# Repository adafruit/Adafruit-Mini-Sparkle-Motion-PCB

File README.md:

## Adafruit Mini Sparkle Motion - WLED-friendly ESP32 NeoPixel LED Driver PCB

<a href="http://www.adafruit.com/products/6160"><br/>
Click here to purchase one from the Adafruit shop</a>

PCB files for the Adafruit Mini Sparkle Motion - WLED-friendly ESP32 NeoPixel LED Driver. 

Format is EagleCAD schematic and board layout
* https://www.adafruit.com/product/6160

### Description

The Adafruit Sparkle Motion Mini is part of our series of "Sparkle Motion" boards, that are our attempt to make the best small WLED-friendly smart LED driving board in the whole world. Our resident mermaid, firepixie makes a lot of projects with WLED and she loves it! So how can we make something that will be powerful enough to drive advanced LED projects that need a compact design?

The Mini version of the Sparkle Motion is a simpler version of our full-featured Sparkle Motion, we give up the high voltage support and built in IR receiver, in order to make it under 1 square inch in size! By using a 4-layer board and double-sided assembly we've put together this feature set:

* Power via USB Type C for up to 5V 4A input - you can use off-the-shelf USB battery packs for portable operation.
* 4 Amp resetting fuse to protect from over-current drive
* ESP32 mini module with built in antenna port - the classic ESP32 has the best WLED support even if we'd prefer the 'S2 or 'S3. Comes with 4 MB of flash, dual core 240MHz Tensilica, WiFi, Bluetooth LE and Bluetooth Classic support.
* USB-serial converter with auto-reset
* Two output signals plus 5V power and ground - both signal output are level shifted to 5V. These are on 0.1" spaced breakout pads. To keep the design slim we don't include terminal blocks pre-soldered, but we do stock the matching blocks if you want them
* Extra 2x3 0.1" breakout pads with 4 more GPIO plus 3V power and ground.
* Built-in I2S microphone
* Stemma QT I2C port to connect external sensors/OLED/etc
* User button on GPIO 0 plus Reset button
* Red built-in LED on pin 12
* Small built-in NeoPixel on pin 18 
* Separate analog/digital input JST port for analog input, potentiometer, microphone or external IR receiver on pin 13
* Compact enough you can use it for wearable projects - 1.2"x0.8" / 30mm x 20mm size with mounting holes

While we recommend it for use with WLED, it will also work just fine as a compact ESP32 board for use with Arduino, ESP-IDF, MicroPython, CircuitPython or any other ESP32 supported codebase. 

Note that unlike the classic Sparkle Motion board, we don't include terminal blocks pre-soldered to keep the board very slim. We do stock the matching blocks if you want them, a small amount of soldering is required to attach them. Also, unlike the bigger version, we dropped the on-board IR receiver - however its easy to add one by plugging in a JST SH 3-pin socket cable and slotting in an IR receiver module.

### License

Adafruit invests time and resources providing this open source design, please support Adafruit and open-source hardware by purchasing products from [Adafruit](https://www.adafruit.com)!

Designed by Limor Fried/Ladyada for Adafruit Industries.

Creative Commons Attribution/Share-Alike, all text above must be included in any redistribution. 
See license.txt for additional details.

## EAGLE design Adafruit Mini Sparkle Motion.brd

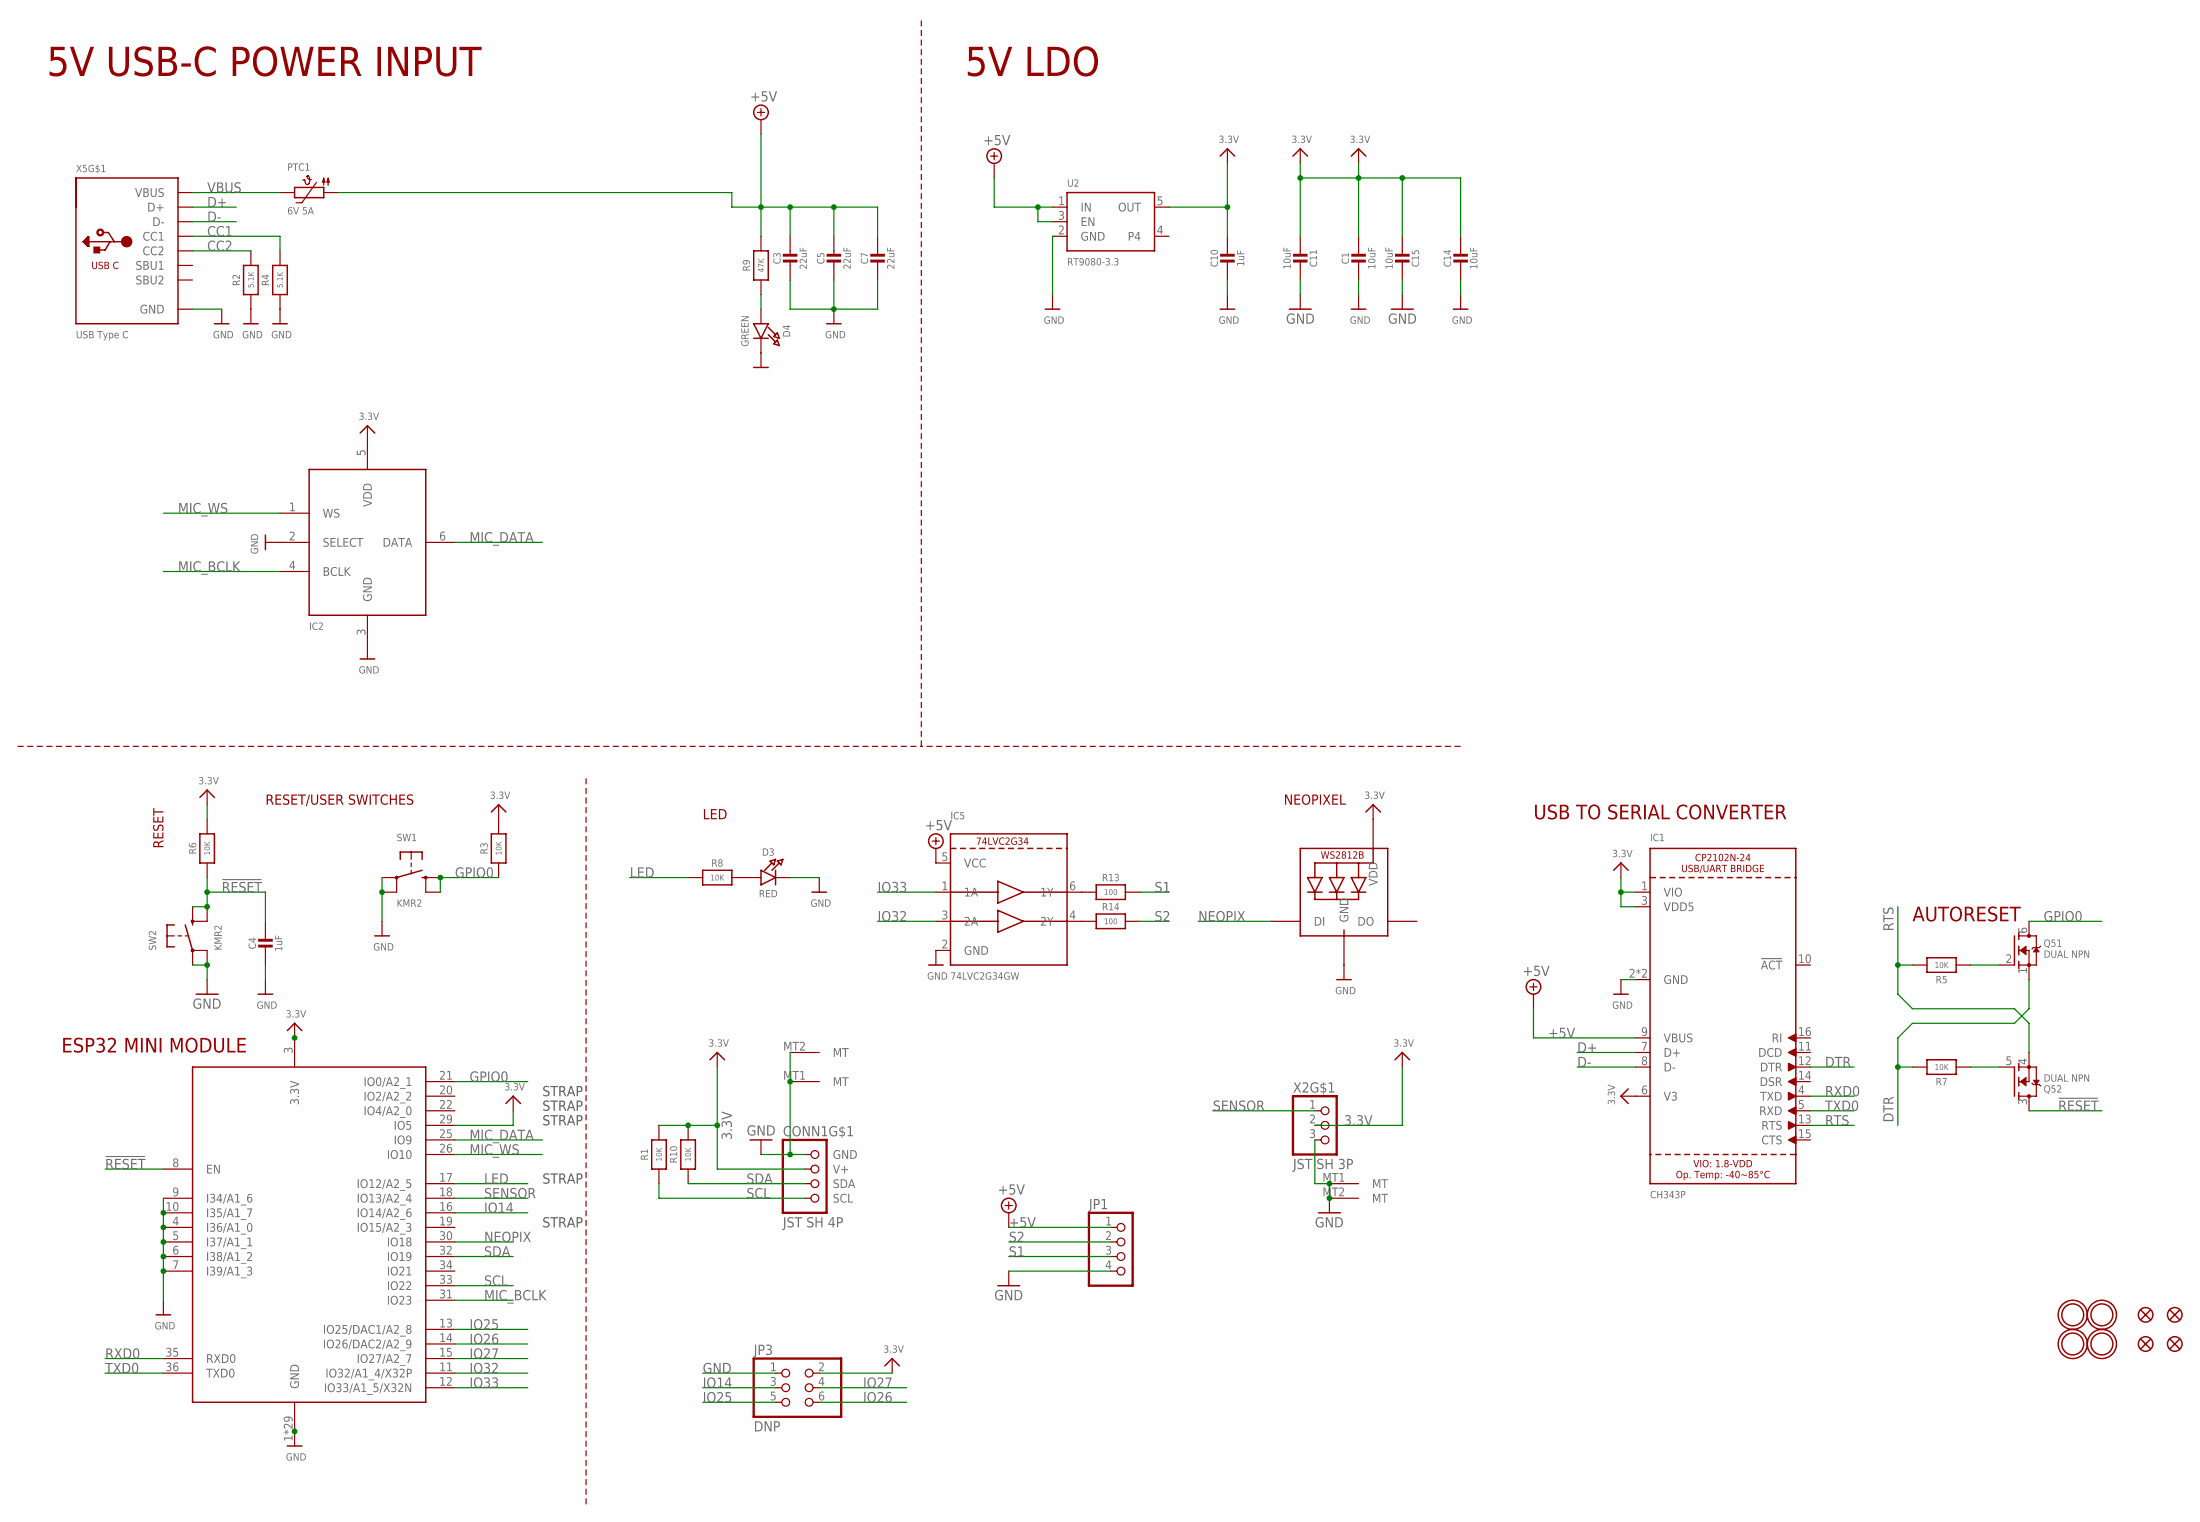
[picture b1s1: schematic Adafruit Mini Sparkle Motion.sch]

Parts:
C1, C11, C14, C15: 10uF; 0805-NO
C3, C5, C7: 22uF; 0805-NO
C4, C10: 1uF; _0402NO
CONN1: JST SH 4P; JST_SH4
D3: RED; CHIPLED_0603_NOOUTLINE
D4: GREEN; CHIPLED_0603_NOOUTLINE
IC1: CH343P; QFN16_3MM
IC2: ICS-43434; SPH0645LM4H
IC5: 74LVC2G34GW; SC70-6L
JP1: HEADER-1X4; 1X04_OVAL
JP3: DNP; 2X03_ROUND_70MIL
LED1: WS2812B_SK6805_1515; SK6805_1515
PTC1: 6V 5A; PTC1210
Q5: DUAL NPN; SOT363; JLC_ROTATION 90
R1, R3, R5, R6, R7, R8, R10: 10K; _0402NO
R2, R4: 5.1K; _0402NO
R9: 47K; _0402NO
R13, R14: 100; _0402NO
SW1, SW2: KMR2; BTN_RKB2_4.6X2.8
U2: RT9080-3.3; SOT23-5; JLC_ROTATION 0
U$14, U$20, U$28, U$31: MOUNTINGHOLE2.5; MOUNTINGHOLE_2.5_PLATED
U$23, U$25, U$34, U$35: FIDUCIAL_0.5MM
X2: JST SH 3P; JST_SH3
X4: ESP32-MINI-1
X5: USB Type C; USB_C_CUSB31-CFM2AX-01-X

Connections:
3.3V: C1.1, C10.1, C11.1, C14.1, C15.1, CONN1.2 (V+), IC1.1 (VIO), IC1.3 (VDD5), IC1.6 (V3), IC2.5 (VDD), JP3.2, LED1.2 (VDD), R1.2, R3.2, R6.2, R10.2, U2.5 (OUT), X2.2, X4.3 (3.3V), X4.29 (IO5)
!RESET: C4.1, Q5.3 (D), R6.1, SW2.B (S), SW2.B' (S1), X4.8 (EN)
+5V: C3.1, C5.1, C7.1, IC1.9 (VBUS), IC5.5 (VCC), JP1.1, PTC1.P$1 (1), R9.2, U2.1 (IN), U2.3 (EN)
CC1: R4.2, X5.A5 (CC1)
CC2: R2.2, X5.B5 (CC2)
D+: IC1.7 (D+), X5.A6 (D+), X5.B6 (D+)
D-: IC1.8 (D-), X5.A7 (D-), X5.B7 (D-)
DTR: IC1.12 (DTR), Q5.1 (S), R7.2
GND: C1.2, C3.2, C4.2, C5.2, C7.2, C10.2, C11.2, C14.2, C15.2, CONN1.1 (GND), CONN1.MT1 (MT), CONN1.MT2 (MT), D3.C, D4.C, IC1.2 (GND), IC1.THERMAL (GND), IC2.2 (SELECT), IC2.3 (GND), IC5.2 (GND), JP1.4, JP3.1, LED1.4 (GND), R2.1, R4.1, SW1.A, SW1.A' (P1), SW2.A, SW2.A' (P1), U2.2 (GND), X2.3, X2.MT1 (MT), X2.MT2 (MT), X4.1 (GND), X4.2 (GND), X4.4 (I36/A1_0), X4.5 (I37/A1_1), X4.6 (I38/A1_2), X4.7 (I39/A1_3), X4.9 (I34/A1_6), X4.10 (I35/A1_7), X4.27 (GND), X4.38 (GND), X4.39 (GND), X4.40 (GND), X4.41 (GND), X4.42 (GND), X4.43 (GND), X4.44 (GND), X4.45 (GND), X4.46 (GND), X4.47 (GND), X4.48 (GND), X4.49 (GND), X4.50 (GND), X4.51 (GND), X4.52 (GND), X4.53 (GND), X4.54 (GND), X4.55 (GND), X4.56 (GND), X4.57 (GND), X4.58 (GND), X4.59 (GND), X4.60 (GND), X4.61 (GND), X4.62 (GND), X4.63 (GND), X5.A1B12 (GND), X5.B1A12 (GND)
GPIO0: Q5.6 (D), R3.1, SW1.B (S), SW1.B' (S1), X4.21 (IO0/A2_1)
IO14: JP3.3, X4.16 (IO14/A2_6)
IO25: JP3.5, X4.13 (IO25/DAC1/A2_8)
IO26: JP3.6, X4.14 (IO26/DAC2/A2_9)
IO27: JP3.4, X4.15 (IO27/A2_7)
IO32: IC5.3 (2A), X4.11 (IO32/A1_4/X32P)
IO33: IC5.1 (1A), X4.12 (IO33/A1_5/X32N)
LED: R8.1, X4.17 (IO12/A2_5)
MIC_BCLK: IC2.4 (BCLK), X4.31 (IO23)
MIC_DATA: IC2.6 (DATA), X4.25 (IO9)
MIC_WS: IC2.1 (WS), X4.26 (IO10)
unnamed: D3.A, R8.2
unnamed: Q5.5 (G), R7.1
unnamed: Q5.2 (G), R5.1
unnamed: IC5.6 (1Y), R13.1
unnamed: IC5.4 (2Y), R14.1
unnamed: D4.A, R9.1
NEOPIX: LED1.1 (DI), X4.30 (IO18)
RTS: IC1.13 (RTS), Q5.4 (S), R5.2
RXD0: IC1.4 (TXD), X4.35 (RXD0)
S1: JP1.3, R13.2
S2: JP1.2, R14.2
SCL: CONN1.4 (SCL), R1.1, X4.33 (IO22)
SDA: CONN1.3 (SDA), R10.1, X4.32 (IO19)
SENSOR: X2.1, X4.18 (IO13/A2_4)
TXD0: IC1.5 (RXD), X4.36 (TXD0)
VBUS: PTC1.P$2 (2), X5.A4B9 (VBUS), X5.B4A9 (VBUS)

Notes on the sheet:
5V USB-C POWER INPUT
RESET
LED
NEOPIXEL
ESP32 MINI MODULE
RESET/USER SWITCHES
AUTORESET
USB TO SERIAL CONVERTER
5V LDO
STRAP

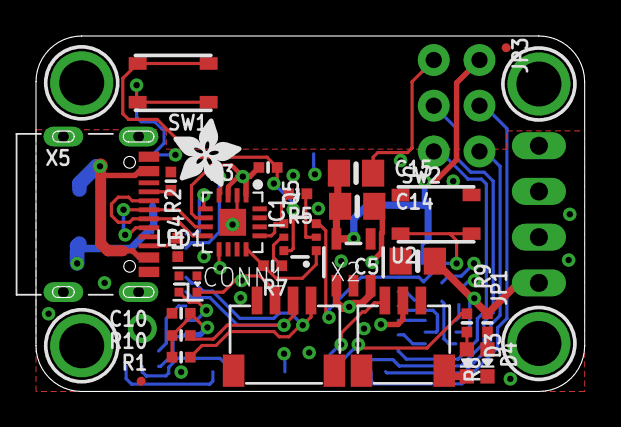
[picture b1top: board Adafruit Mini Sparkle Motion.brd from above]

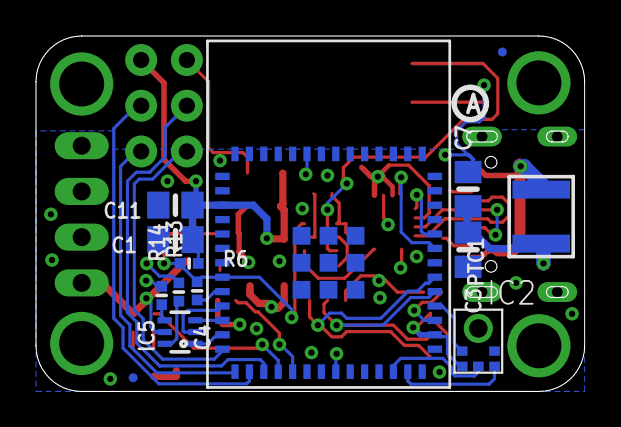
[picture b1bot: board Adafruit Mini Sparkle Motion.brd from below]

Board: 4 copper layers, 30.5 x 19.7 mm, 68 parts (22 on the bottom side), 36 nets.

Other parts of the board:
PLABEL0: PLABEL0
PLABEL1: PLABEL1
PLABEL2: PLABEL2
PLABEL3: PLABEL3
PLABEL4: PLABEL4
PLABEL5: PLABEL5
PLABEL6: PLABEL6
PLABEL7: PLABEL7
PLABEL8: PLABEL8
PLABEL9: PLABEL9
PLABEL10: PLABEL10
PLABEL11: PLABEL11
PLABEL15: PLABEL15
PLABEL16: PLABEL16
PLABEL17: PLABEL17
PLABEL18: PLABEL18
PLABEL20: PLABEL20
PLABEL21: PLABEL21
PLABEL22: PLABEL22
PLABEL23: PLABEL23
U$27: ADAFRUIT_3.5MM
U$29: PCBFEAT-REV-040

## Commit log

2025-01-15 cookiecutter
2025-01-16 prettypins
2025-01-24 add A0

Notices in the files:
parts and their libraries:
microbuilder: This work is placed in the public domain, and may be freely used for commercial and non-commercial work with the following conditions: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
